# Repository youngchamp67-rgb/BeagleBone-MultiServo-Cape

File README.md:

# BeagleBone-MultiServo-Cape
This repo contains KiCad files for a BBB robotics cape. High-torque motors (like 12 MG995 servos) draw 15+ amps, causing voltage drops and processor crashes on standard proto boards. This extension board solves this by adding a power distribution circuit to the BBB, safely handling massive currents for rugged applications.

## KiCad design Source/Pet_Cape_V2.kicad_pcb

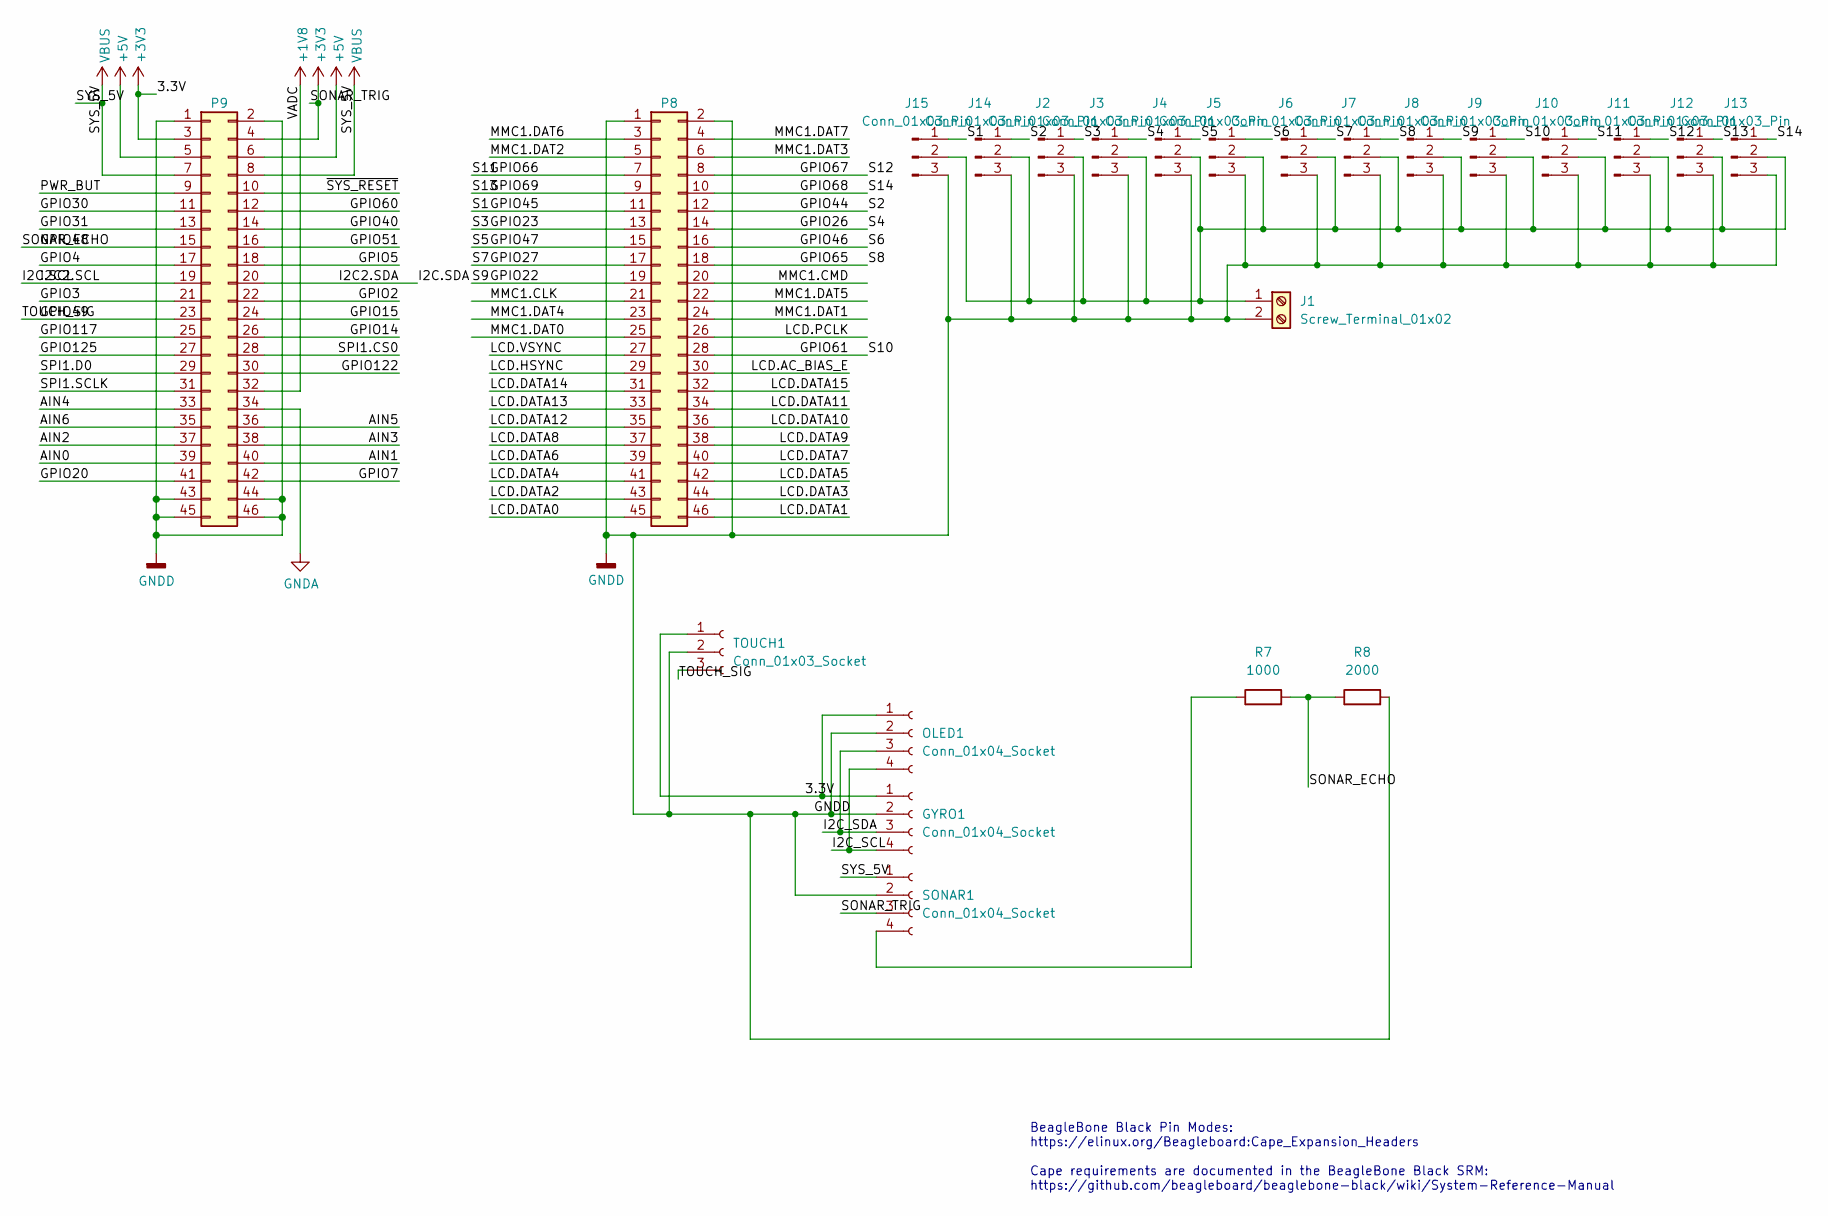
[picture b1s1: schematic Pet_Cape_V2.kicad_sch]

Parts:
GYRO1: Conn_01x04_Socket; PinSocket_1x04_P2.54mm_Vertical
J1: Screw_Terminal_01x02; TerminalBlock_Phoenix_MKDS-1,5-2-5.08_1x02_P5.08mm_Horizont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
J2, J3, J4, J5, J6, J7, J8, J9, J10, J11, J12, J13, J14, J15: Conn_01x03_Pin; PinHeader_1x03_P2.54mm_Vertical
OLED1: Conn_01x04_Socket; PinSocket_1x04_P2.54mm_Vertical
P8, P9: BeagleBone_Black_Header; PinHeader_2x23_P2.54mm_Vertical
R7: 1000; R_Axial_DIN0207_L6.3mm_D2.5mm_P10.16mm_Horizontal
R8: 2000; R_Axial_DIN0207_L6.3mm_D2.5mm_P10.16mm_Horizontal
SONAR1: Conn_01x04_Socket; PinSocket_1x04_P2.54mm_Vertical
TOUCH1: Conn_01x03_Socket; PinSocket_1x03_P2.54mm_Vertical

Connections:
+1V8: P9.32
+3V3: GYRO1.1, OLED1.1, P9.3, P9.4, SONAR1.3, TOUCH1.1; also elsewhere on the board
+5V: P9.5, P9.6
/AIN0: P9.39
/AIN1: P9.40
/AIN2: P9.37
/AIN3: P9.38
/AIN4: P9.33
/AIN5: P9.36
/AIN6: P9.35
/GPIO2: P9.22
/GPIO3: P9.21
/GPIO4: P9.17
/GPIO5: P9.18
/GPIO7: P9.42
/GPIO14: P9.26
/GPIO15: P9.24
/GPIO20: P9.41
/GPIO22: J8.1, P8.19
/GPIO23: J2.1, P8.13
/GPIO26: J3.1, P8.14
/GPIO27: J6.1, P8.17
/GPIO30: P9.11
/GPIO31: P9.13
/GPIO40: P9.14
/GPIO44: J14.1, P8.12
/GPIO45: J15.1, P8.11
/GPIO46: J5.1, P8.16
/GPIO47: J4.1, P8.15
/GPIO48: P9.15, R7.2, R8.1
/GPIO49: P9.23, TOUCH1.3
/GPIO51: P9.16
/GPIO60: P9.12
/GPIO61: J9.1, P8.28
/GPIO65: J7.1, P8.18
/GPIO66: J10.1, P8.7
/GPIO67: J11.1, P8.8
/GPIO68: J13.1, P8.10
/GPIO69: J12.1, P8.9
/GPIO117: P9.25
/GPIO122: P9.30
/GPIO125: P9.27
/I2C.SCL: P9.19
/I2C.SDA: P9.20
/I2C_SCL: GYRO1.4, OLED1.4; also elsewhere on the board
/I2C_SDA: GYRO1.3, OLED1.3; also elsewhere on the board
/LCD.AC_BIAS_E: P8.30
/LCD.DATA0: P8.45
/LCD.DATA1: P8.46
/LCD.DATA2: P8.43
/LCD.DATA3: P8.44
/LCD.DATA4: P8.41
/LCD.DATA5: P8.42
/LCD.DATA6: P8.39
/LCD.DATA7: P8.40
/LCD.DATA8: P8.37
/LCD.DATA9: P8.38
/LCD.DATA10: P8.36
/LCD.DATA11: P8.34
/LCD.DATA12: P8.35
/LCD.DATA13: P8.33
/LCD.DATA14: P8.31
/LCD.DATA15: P8.32
/LCD.HSYNC: P8.29
/LCD.PCLK: P8.26
/LCD.VSYNC: P8.27
/MMC1.CLK: P8.21
/MMC1.CMD: P8.20
/MMC1.DAT0: P8.25
/MMC1.DAT1: P8.24
/MMC1.DAT2: P8.5
/MMC1.DAT3: P8.6
/MMC1.DAT4: P8.23
/MMC1.DAT5: P8.22
/MMC1.DAT6: P8.3
/MMC1.DAT7: P8.4
/PWR_BUT: P9.9
/SPI1.CS0: P9.28
/SPI1.D0: P9.29
/SPI1.SCLK: P9.31
/~SYS_RESET: P9.10
GNDA: P9.34
GNDD: GYRO1.2, J1.2, J2.3, J3.3, J4.3, J5.3, J6.3, J7.3, J8.3, J9.3, J10.3, J11.3, J12.3, J13.3, J14.3, J15.3, OLED1.2, P8.1, P8.2, P9.1, P9.2, P9.43, P9.44, P9.45, P9.46, R8.2, SONAR1.2, TOUCH1.2; also elsewhere on the board
unnamed: J1.1, J2.2, J3.2, J4.2, J5.2, J6.2, J7.2, J8.2, J9.2, J10.2, J11.2, J12.2, J13.2, J14.2, J15.2
unnamed: R7.1, SONAR1.4
VBUS: P9.7, P9.8, SONAR1.1

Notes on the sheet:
BeagleBone Black Pin Modes: https://elinux.org/Beagleboard:Cape_Expansion_Headers Cape requirements are documented in the BeagleBone Black SRM: https://github.com/beagleboard/beaglebone-black/wiki/System-Reference-Manual

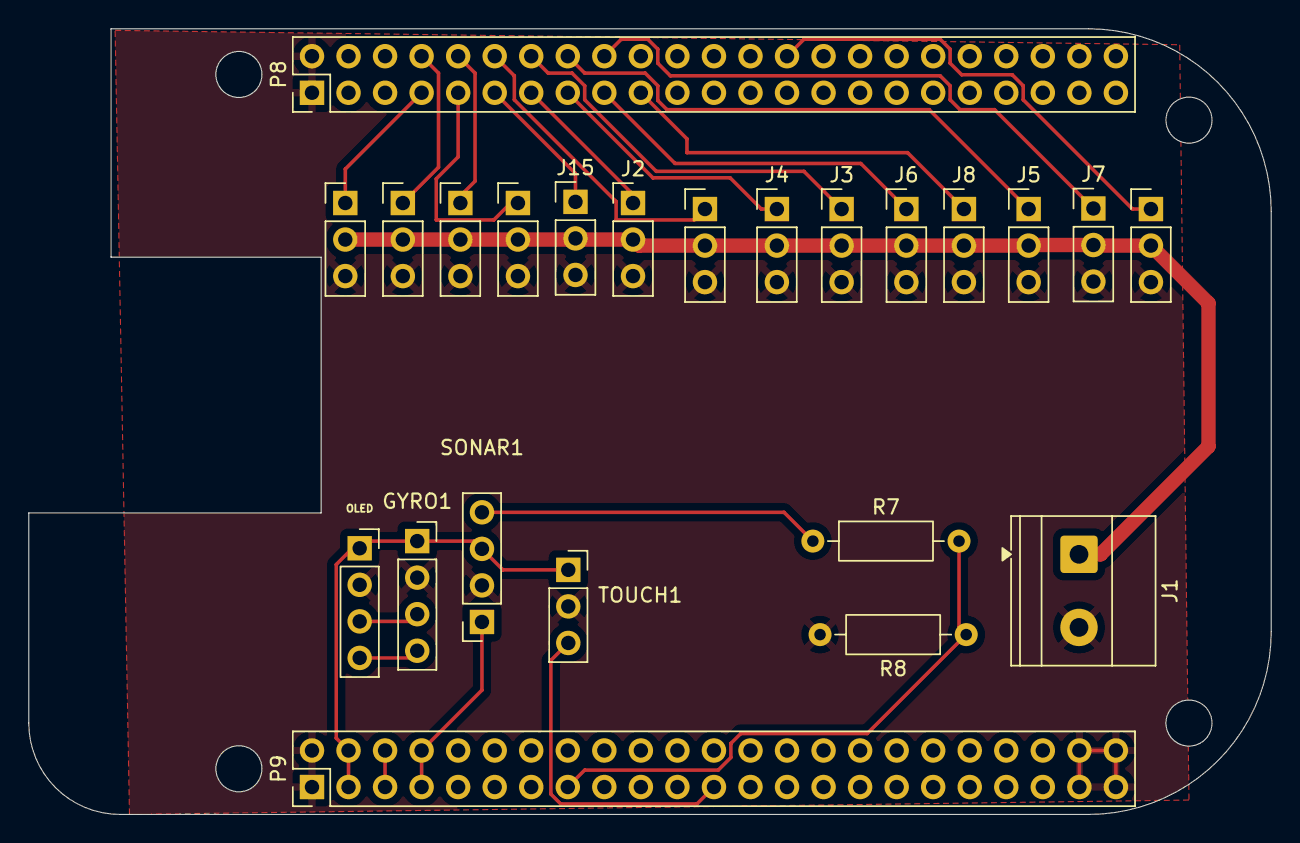
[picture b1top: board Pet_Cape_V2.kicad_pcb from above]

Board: 2 copper layers, 86.4 x 54.6 mm, 27 parts (0 on the bottom side), 24 nets.

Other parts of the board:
MH1, MH2, MH3, MH4: MountingHole_3.2mm_M3_DIN965
OLED: Conn_01x04_Socket; PinSocket_1x04_P2.54mm_Vertical

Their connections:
+3V3: OLED.1; also elsewhere on the board
/I2C_SCL: OLED.4; also elsewhere on the board
/I2C_SDA: OLED.3; also elsewhere on the board
GNDD: OLED.2; also elsewhere on the board

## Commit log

2026-06-19 Create Fabrication
2026-06-19 Create Source
2026-06-19 Create Docs
2026-06-19 Create LICENSE
2026-06-19 Add MIT License to the project
2026-06-19 Update LICENSE
